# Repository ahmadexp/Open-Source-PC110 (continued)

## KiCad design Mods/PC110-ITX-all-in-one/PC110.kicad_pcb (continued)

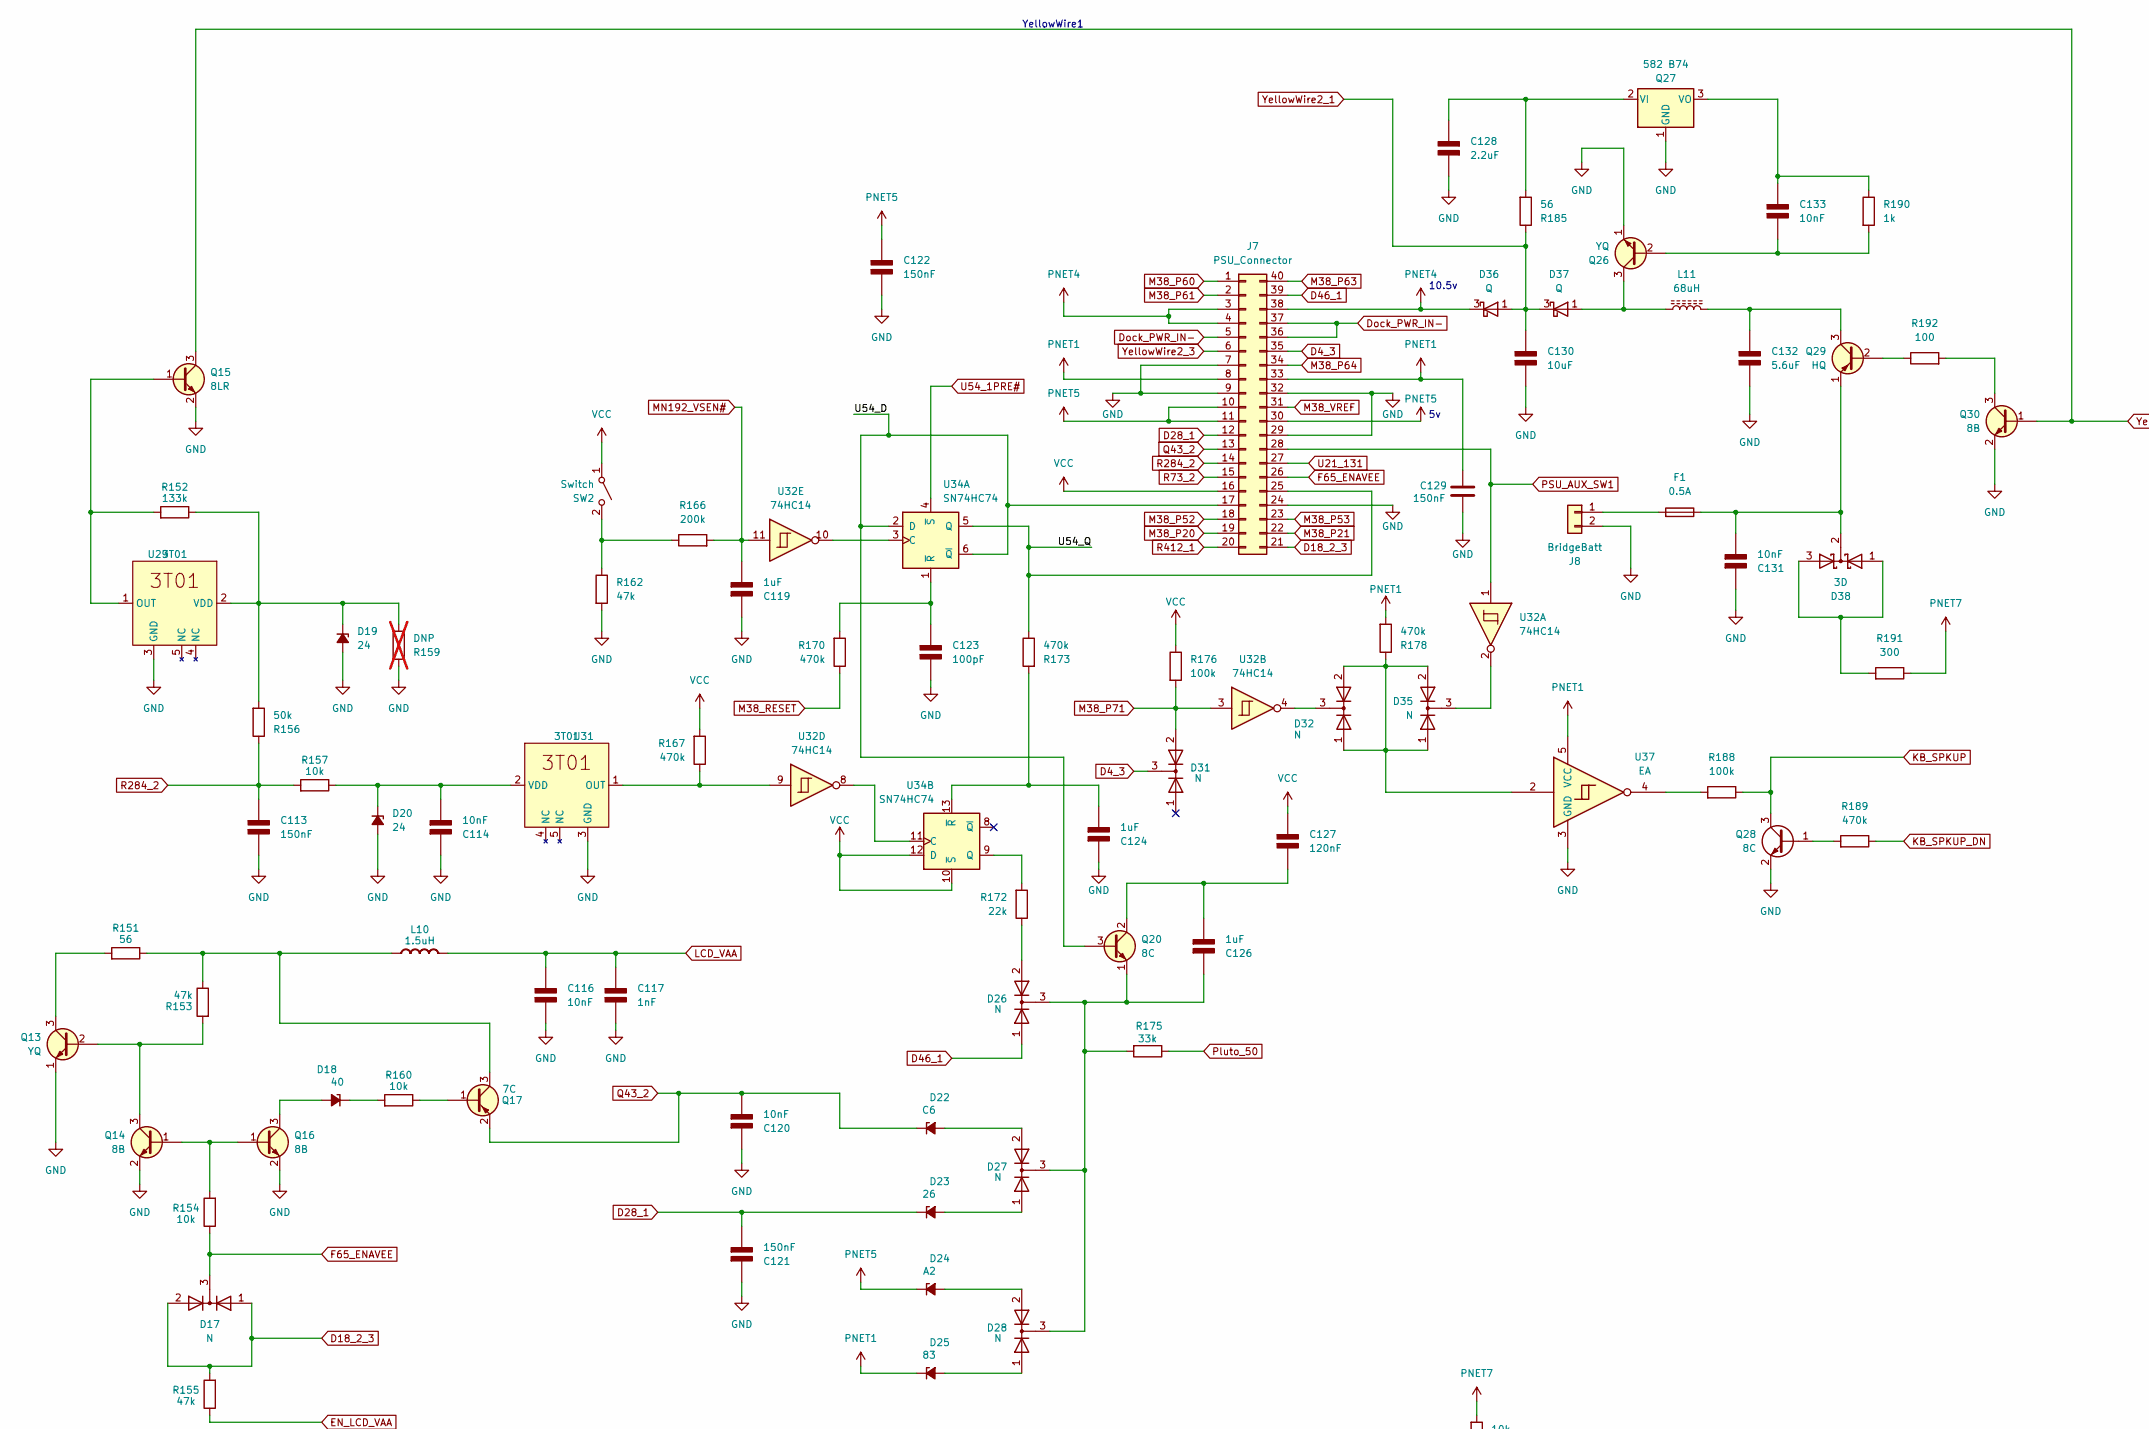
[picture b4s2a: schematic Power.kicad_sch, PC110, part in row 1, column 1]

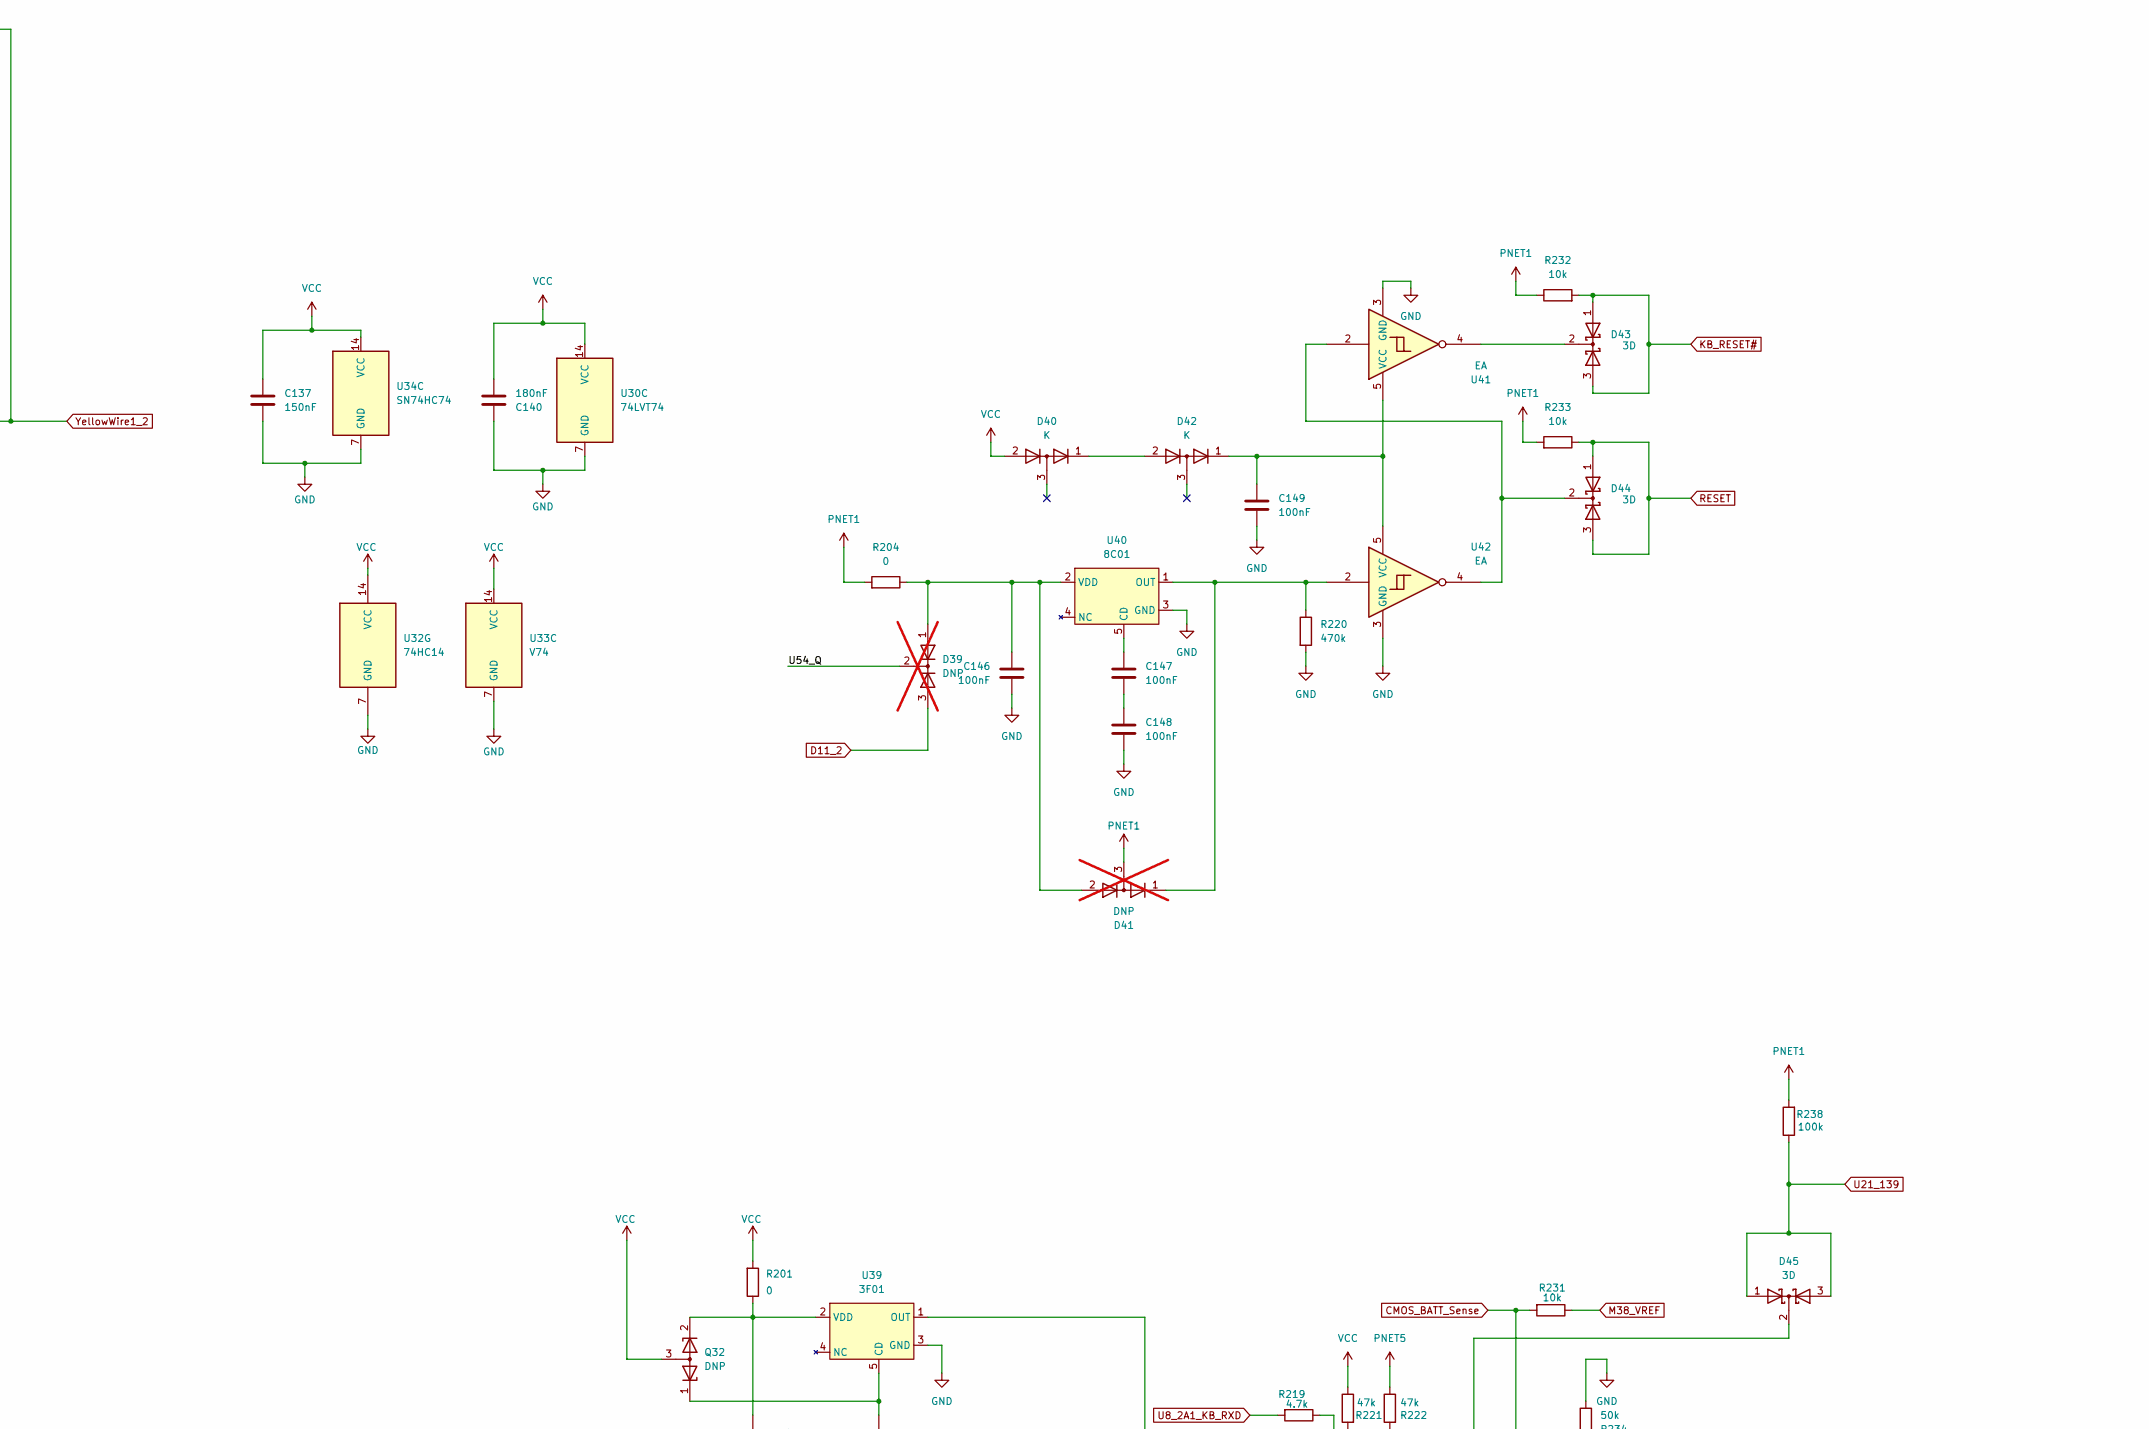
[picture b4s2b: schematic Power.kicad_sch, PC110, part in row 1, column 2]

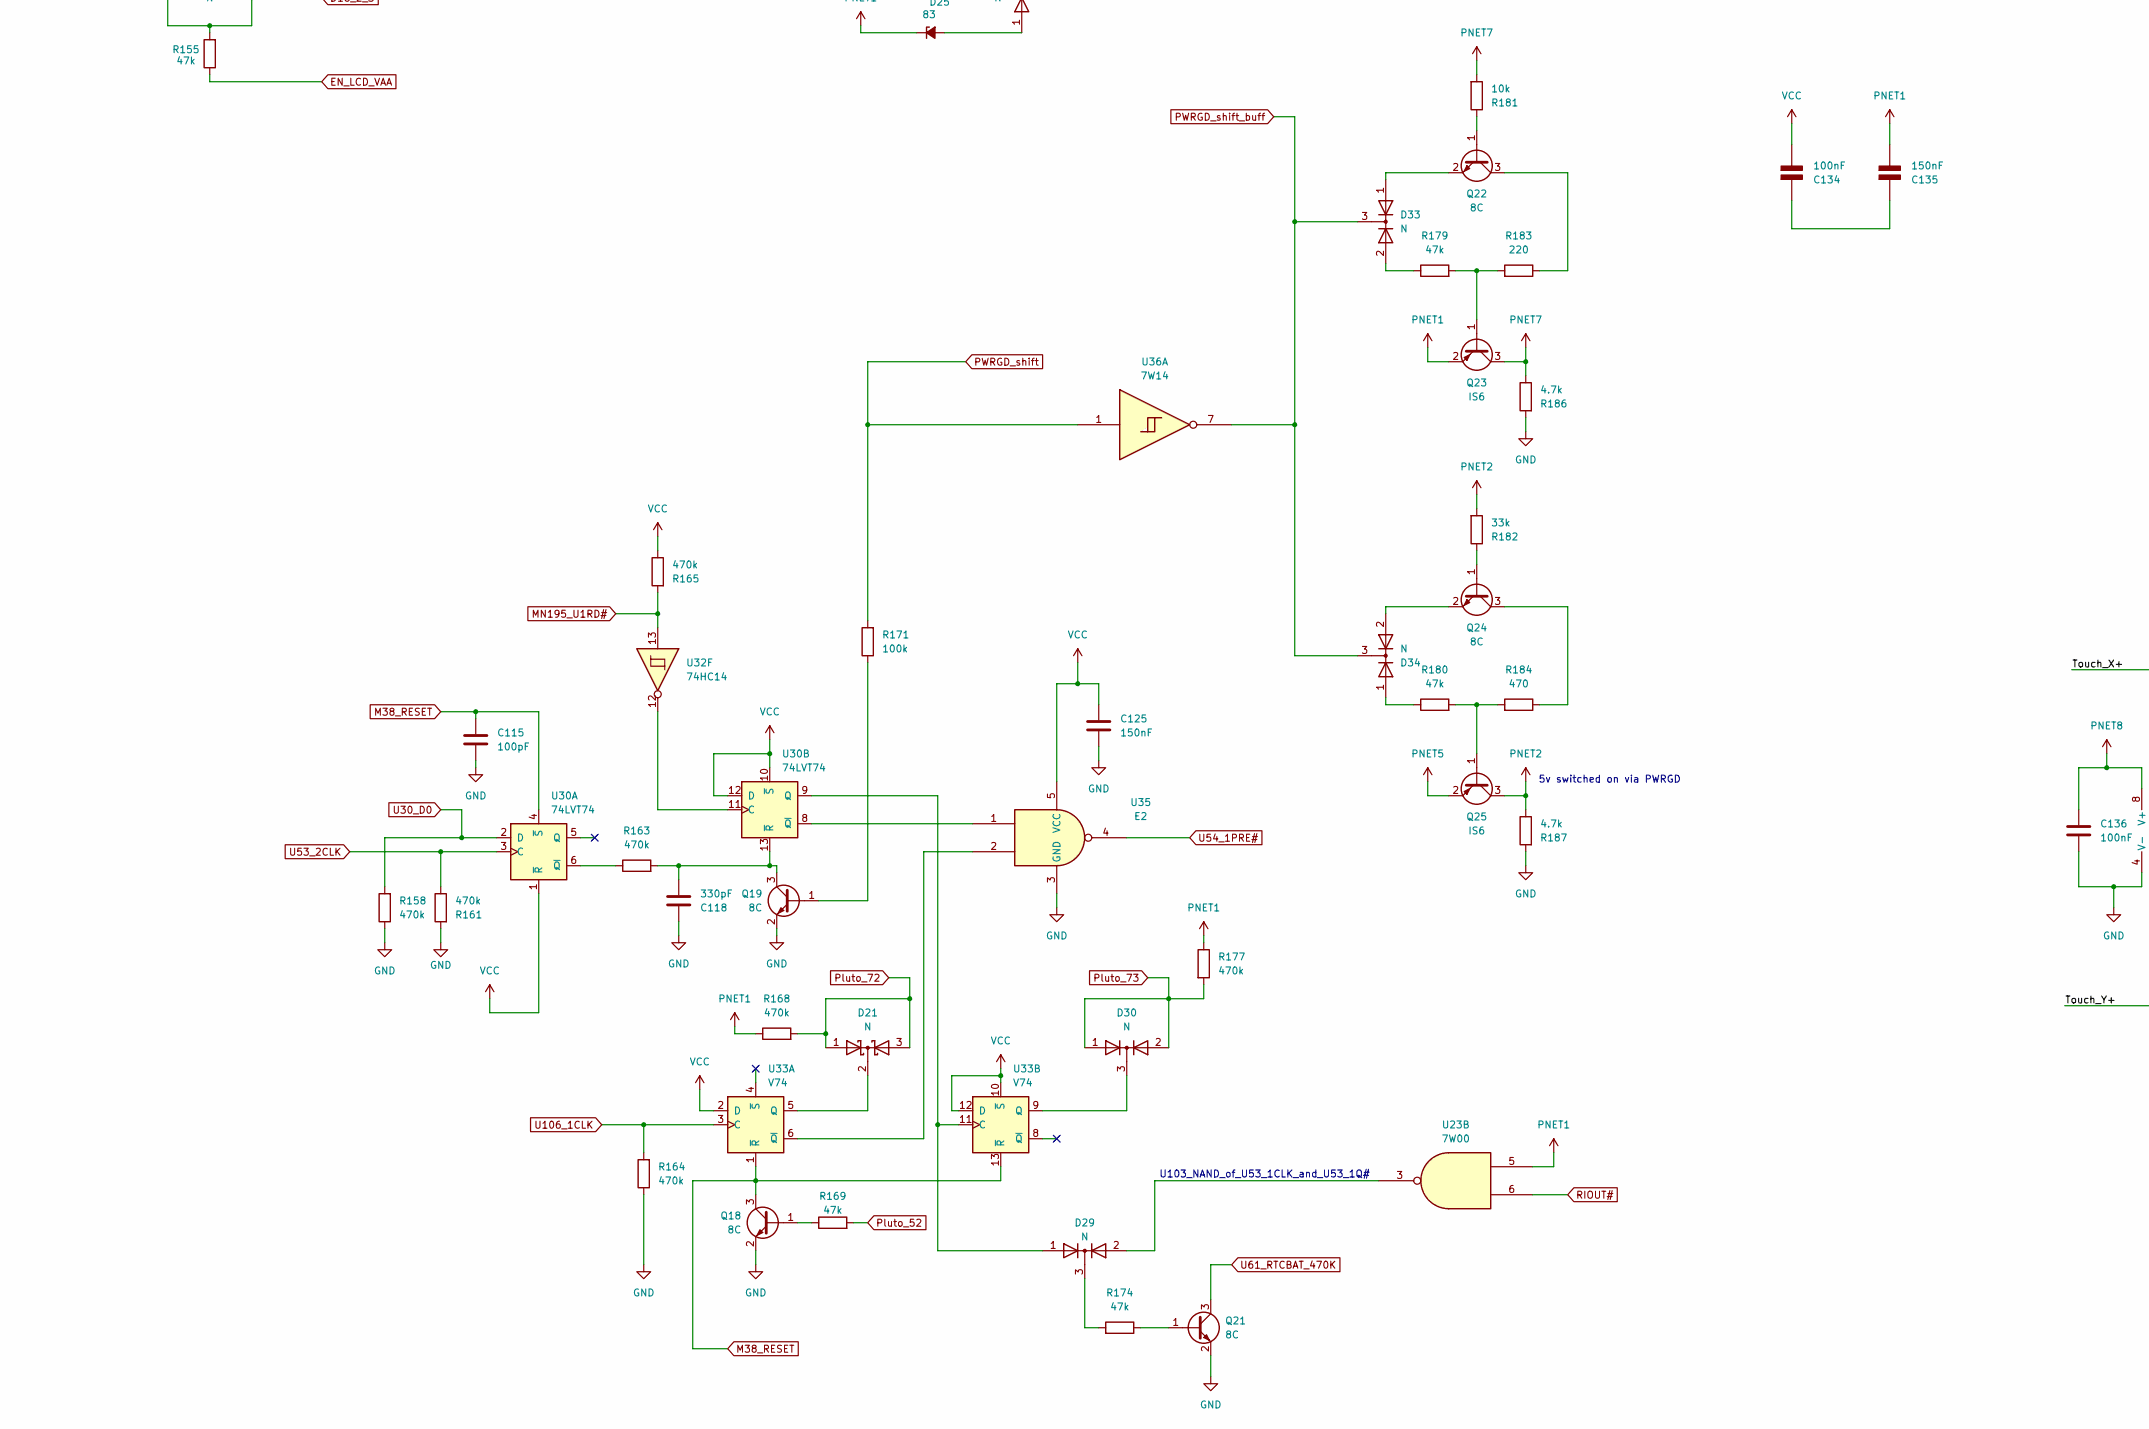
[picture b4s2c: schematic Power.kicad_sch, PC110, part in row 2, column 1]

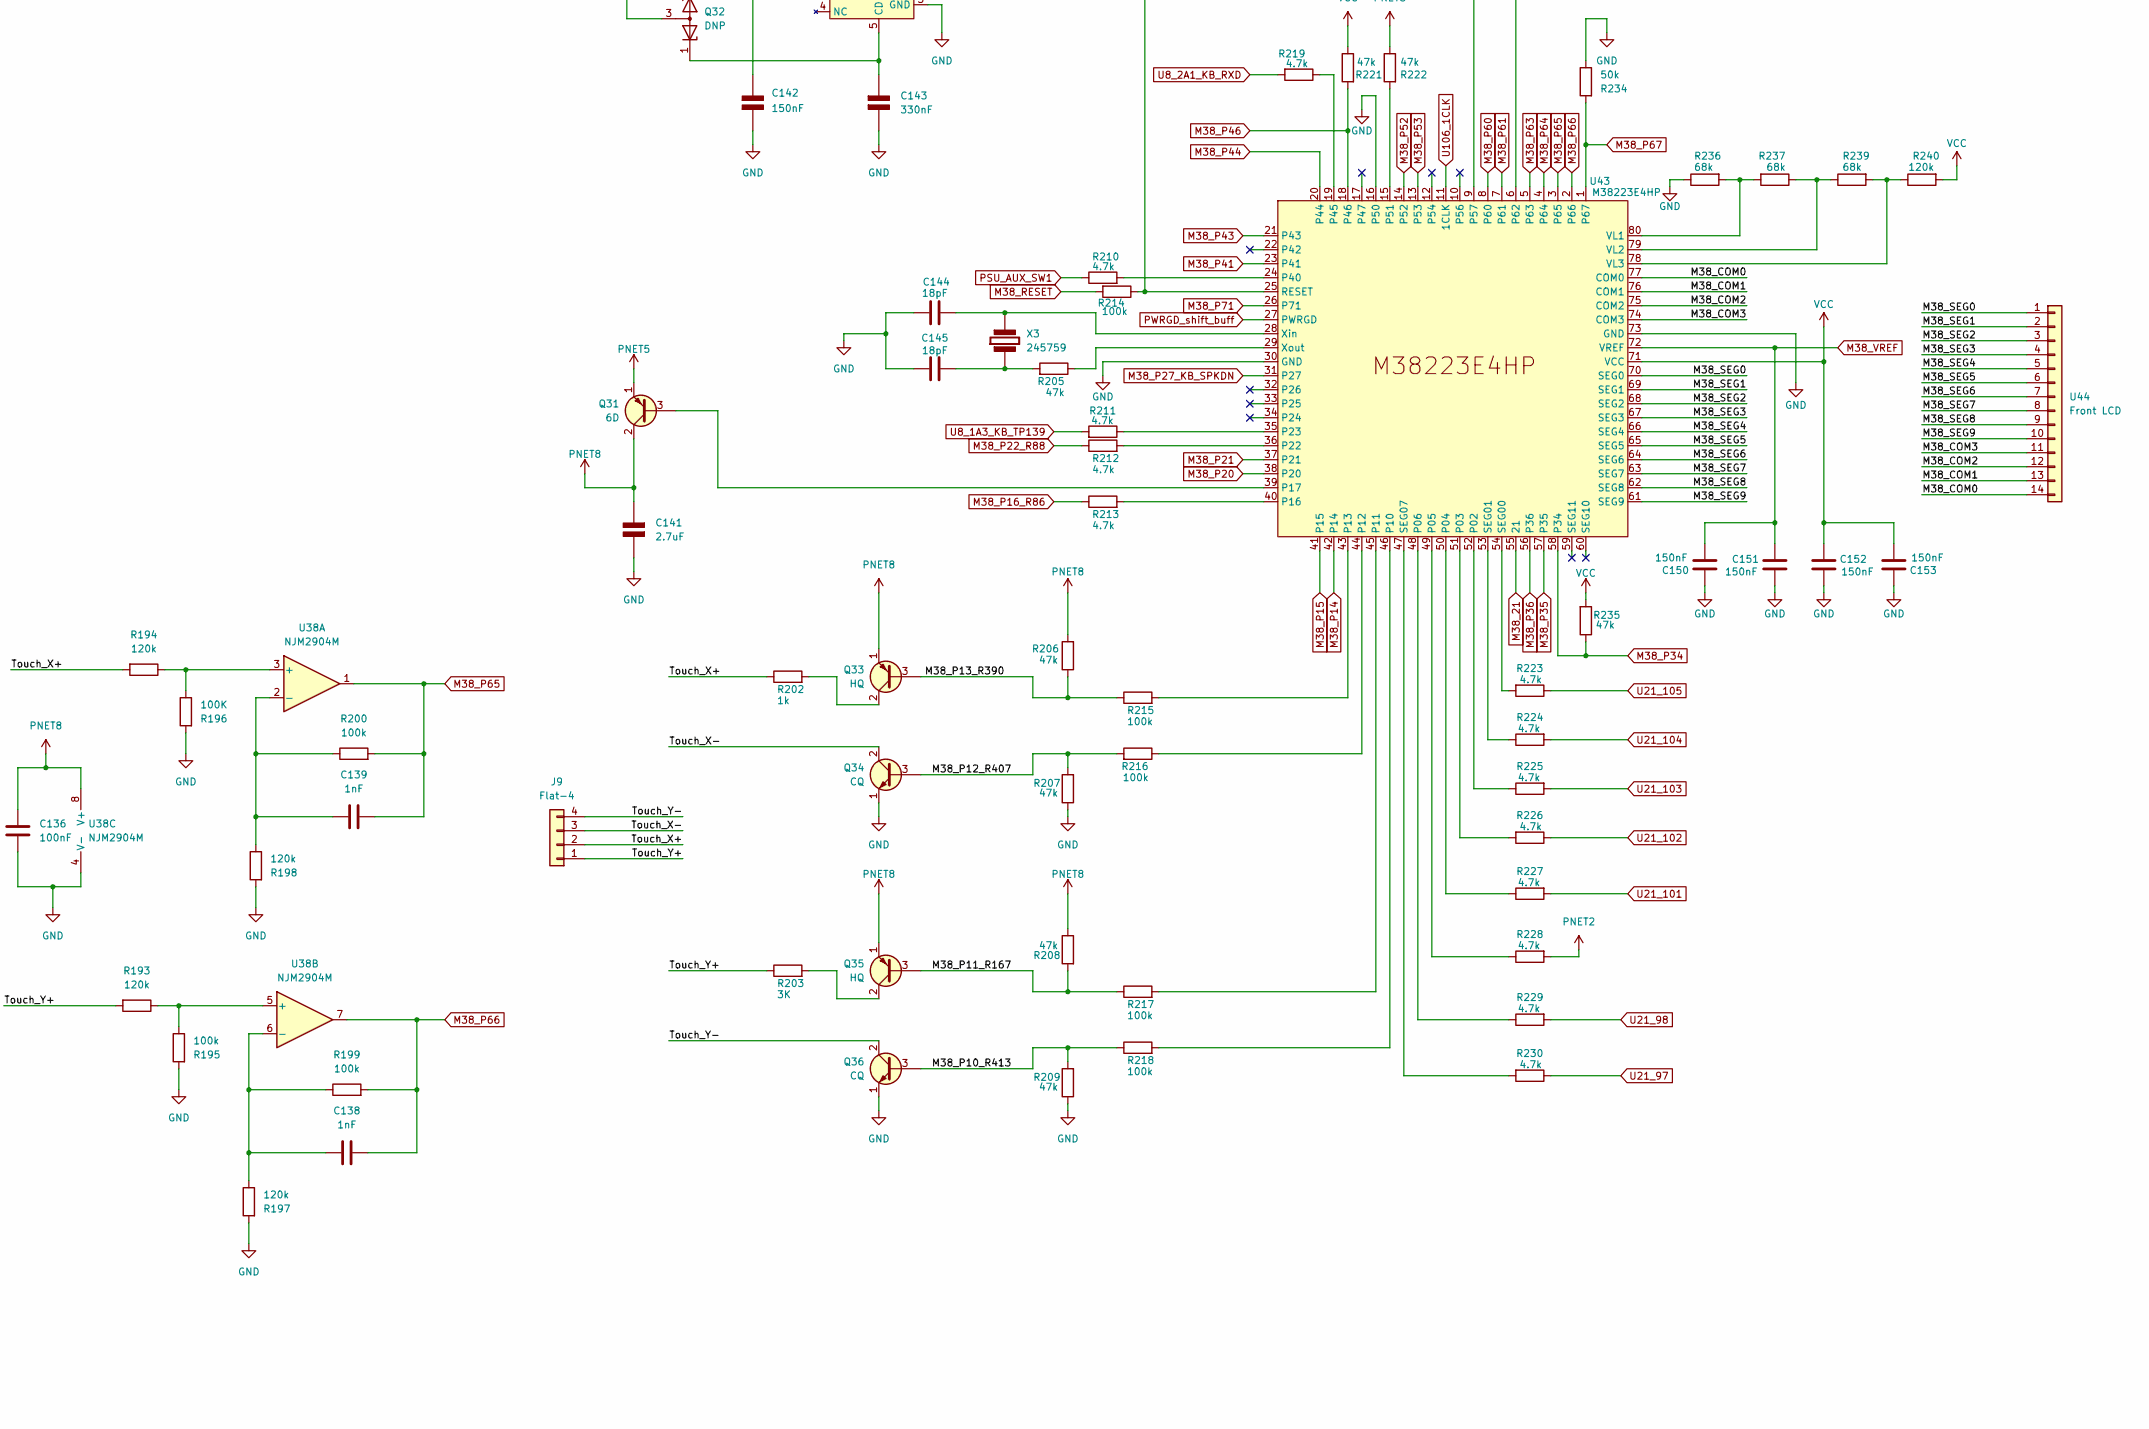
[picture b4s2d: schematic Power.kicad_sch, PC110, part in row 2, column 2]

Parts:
C113, C121: 150nF; C_0603_1608Metric
C114, C116, C120, C131, C133: 10nF; C_0603_1608Metric
C115, C123: 100pF; C_0402_1005Metric
C117, C138, C139: 1nF; C_0402_1005Metric
C118: 330pF; C_0402_1005Metric
C119, C124, C126: 1uF; C_0603_1608Metric
C122, C125, C129, C135, C137, C142, C150, C151, C152, C153: 150nF; C_0402_1005Metric
C127: 120nF; C_0402_1005Metric
C128: 2.2uF; C_0805_2012Metric
C130: 10uF; C_1206_3216Metric
C132: 5.6uF; C_1206_3216Metric
C134, C136, C146, C149: 100nF; C_0402_1005Metric
C140: 180nF; C_0402_1005Metric
C141: 2.7uF; C_0805_2012Metric
C143: 330nF; C_0603_1608Metric
C144, C145: 18pF; C_0402_1005Metric
C147, C148: 100nF; C_0603_1608Metric
D17, D21, D26, D27, D28, D29, D30, D31, D32, D33, D34, D35: N; SOT-416L
D18: 40; D_0603_1608Metric
D19, D20: 24; D_0603_1608Metric
D22: C6; D_0603_1608Metric
D23: 26; D_0603_1608Metric
D24: A2; D_0603_1608Metric
D25: 83; D_0603_1608Metric
D36, D37: Q; 3D
D38, D43, D44: 3D
D39, D41: DNP; 3D; not fitted
D40, D42: K; SOT-416L
D45: 3D; SOT-23
F1: 0.5A; Fuse_1206_3216Metric
J7: PSU_Connector
J8: BridgeBatt
J9: Flat-4
L10: 1.5uH; L_0603_1608Metric
L11: 68uH; L_1210_3225Metric
Q13, Q26: YQ; SOT-416L
Q14, Q16, Q30: 8B; SOT-416
Q15: 8LR; SOT-416
Q17: 7C; TSOT-23
Q18, Q19, Q20, Q21, Q22, Q28: 8C; SOT-416
Q23, Q25: IS6; SOT-23
Q24: 8C; SOT-523
Q27: 582 B74; SOT-89-3
Q29: HQ; SOT-416L
Q31: 6D; 3D
Q32: DNP; SOT-23
Q33, Q35: HQ; TSOT-23
Q34, Q36: CQ; TSOT-23
R151: 56; R_0603_1608Metric
R152: 133k; R_0402_1005Metric
R153, R155, R162, R169, R174, R179, R180, R205, R206, R207, R208, R209, R221, R222, R235: 47k; R_0402_1005Metric
R154, R157, R160, R181, R231, R232, R233: 10k; R_0402_1005Metric
R156, R234: 50k; R_0402_1005Metric
R158, R161, R163, R164, R165, R167, R168, R170, R173, R177, R178, R189, R220: 470k; R_0402_1005Metric
R159: DNP; R_0402_1005Metric; not fitted
R166: 200k; R_0402_1005Metric
R171, R176, R188, R195, R199, R200, R214, R215, R216, R217, R218, R238: 100k; R_0402_1005Metric
R172: 22k; R_0402_1005Metric
R175, R182: 33k; R_0402_1005Metric
R183: 220; R_0402_1005Metric
R184: 470; R_0402_1005Metric
R185: 56; R_0805_2012Metric
R186, R187, R210, R211, R212, R213, R219, R223, R224, R225, R226, R227, R228, R229, R230: 4.7k; R_0402_1005Metric
R190, R202: 1k; R_0402_1005Metric
R191: 300; R_0805_2012Metric
R192: 100; R_0603_1608Metric
R193, R194, R197, R198, R240: 120k; R_0402_1005Metric
R196: 100K; R_0402_1005Metric
R201, R204: 0; R_0402_1005Metric
R203: 3K; R_0402_1005Metric
R236, R237, R239: 68k; R_0402_1005Metric
SW2: Switch
U23: 7W00; sso-8
U29: 3T01; SOT-23-5
U30: 74LVT74; TSSOP-14_4.4x5mm_P0.65mm
U31: 3T01; TSOP-5_1.65x3.05mm_P0.95mm
U32: 74HC14; TSSOP-14_4.4x5mm_P0.65mm
U33: V74; TSSOP-14_4.4x5mm_P0.65mm
U34: SN74HC74; TSSOP-14_4.4x5mm_P0.65mm
U35: E2; SOT-353
U36: 7W14; sso-8
U37, U41, U42: EA; SOT-353
U38: NJM2904M; soic-8-small
U39: 3F01; TSOP-5_1.65x3.05mm_P0.95mm
U40: 8C01; SOT-23-5
U43: M38223E4HP; QFN-80
U44: Front LCD; LCD
X3: 245759; XTAL-2

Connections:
/Power/M38_COM0: U43.77 (COM0), U44.14
/Power/M38_COM1: U43.76 (COM1), U44.13
/Power/M38_COM2: U43.75 (COM2), U44.12
/Power/M38_COM3: U43.74 (COM3), U44.11
/Power/M38_P10_R413: Q36.3 (B), R209.2, R218.1
/Power/M38_P11_R167: Q35.3 (B), R208.2, R217.1
/Power/M38_P12_R407: Q34.3 (B), R207.2, R216.2
/Power/M38_P13_R390: Q33.3 (B), R206.1, R215.1
/Power/M38_SEG0: U43.70 (SEG0), U44.1
/Power/M38_SEG1: U43.69 (SEG1), U44.2
/Power/M38_SEG2: U43.68 (SEG2), U44.3
/Power/M38_SEG3: U43.67 (SEG3), U44.4
/Power/M38_SEG4: U43.66 (SEG4), U44.5
/Power/M38_SEG5: U43.65 (SEG5), U44.6
/Power/M38_SEG6: U43.64 (SEG6), U44.7
/Power/M38_SEG7: U43.63 (SEG7), U44.8
/Power/M38_SEG8: U43.62 (SEG8), U44.9
/Power/M38_SEG9: U43.61 (SEG9), U44.10
/Power/Touch_X+: J9.2, R194.2, R202.1
/Power/Touch_X-: J9.3, Q34.2 (C)
/Power/Touch_Y+: J9.1, R193.2, R203.1
/Power/Touch_Y-: J9.4, Q36.2 (C)
/Power/U54_D: J7.17, Q20.3 (B), U34.2 (D), U34.6 (~Q)
/Power/U54_Q: D39.2 (K), J7.25, R173.1, U34.5 (Q)
CMOS_BATT_Sense: R231.2, U43.6 (P62); also elsewhere on the board
D4_3: D31.3, J7.35; also elsewhere on the board
D11_2: D39.3 (A); also elsewhere on the board
D18_2_3: D17.1, D17.2, J7.21, R155.2; also elsewhere on the board
D28_1: C121.2 (-), D23.1 (K), J7.12; also elsewhere on the board
D46_1: D26.1, J7.39; also elsewhere on the board
Dock_PWR_IN-: J7.5, J7.36, J7.37; also elsewhere on the board
EN_LCD_VAA: R155.1; also elsewhere on the board
F65_ENAVEE: D17.3, J7.26, R154.1; also elsewhere on the board
GND: C113.2 (-), C114.1 (+), C115.1, C116.2 (-), C117.2 (-), C118.2, C119.1 (+), C120.1 (+), C121.1 (+), C122.2 (-), C123.2 (-), C124.1 (+), C125.1, C128.1 (+), C129.2, C130.2 (-), C131.1 (+), C132.2 (-), C136.1, C137.1, C140.2, C141.2 (-), C142.1 (+), C143.2 (-), C144.2, C145.2, C146.1, C148.1, C149.1, C150.1, C151.2, C152.2, C153.1, D19.2 (A), D20.2 (A), J7.7, J7.9, J7.24, J7.29, J7.32, J8.2, Q13.1 (E), Q14.2 (E), Q15.2 (E), Q16.2 (E), Q18.2 (E), Q19.2 (E), Q21.2 (E), Q26.1 (E), Q27.1 (GND), Q28.2 (E), Q30.2 (E), Q34.1 (E), Q36.1 (E), R158.1, R159.1, R161.2, R162.2, R164.1, R186.2, R187.2, R195.2, R196.2, R197.2, R198.2, R207.1, R209.1, R220.2, R234.1, R236.1, U29.3 (GND), U30.7 (GND), U31.3 (GND), U32.7 (GND), U33.7 (GND), U34.7 (GND), U35.3 (GND), U37.3 (GND), U38.4 (V-), U39.3 (GND), U40.3 (GND), U41.3 (GND), U42.3 (GND), U43.16 (P50), U43.30 (GND), U43.73 (GND); also elsewhere on the board
KB_RESET#: D43.1 (A), D43.3 (A), R232.2; also elsewhere on the board
KB_SPKUP: Q28.3 (C), R188.1; also elsewhere on the board
KB_SPKUP_DN: R189.1; also elsewhere on the board
LCD_VAA: C116.1 (+), C117.1 (+), L10.1 (+); also elsewhere on the board
M38_21: U43.55 (21); also elsewhere on the board
M38_P14: U43.42 (P14); also elsewhere on the board
M38_P15: U43.41 (P15); also elsewhere on the board
M38_P16_R86: R213.1
M38_P20: J7.19, U43.38 (P20); also elsewhere on the board
M38_P21: J7.22, U43.37 (P21); also elsewhere on the board
M38_P22_R88: R212.1; also elsewhere on the board
M38_P27_KB_SPKDN: U43.31 (P27); also elsewhere on the board
M38_P35: U43.57 (P35); also elsewhere on the board
M38_P36: U43.56 (P36); also elsewhere on the board
M38_P41: U43.23 (P41); also elsewhere on the board
M38_P43: U43.21 (P43); also elsewhere on the board
M38_P44: U43.20 (P44); also elsewhere on the board
M38_P52: J7.18, U43.14 (P52); also elsewhere on the board
M38_P53: J7.23, U43.13 (P53); also elsewhere on the board
M38_P60: J7.1, U43.8 (P60); also elsewhere on the board
M38_P61: J7.2, U43.7 (P61); also elsewhere on the board
M38_P63: J7.40, U43.5 (P63); also elsewhere on the board
M38_P64: J7.34, U43.4 (P64); also elsewhere on the board
M38_P65: C139.2, R200.2, U38.1, U43.3 (P65)
M38_P66: C138.2, R199.2, U38.7, U43.2 (P66)
M38_P67: R234.2, U43.1 (P67)
M38_P71: D31.2, R176.2, U32.3, U43.26 (P71)
M38_RESET: C115.2, Q18.3 (C), R170.1, R214.2, U30.4 (~S), U33.1 (~R), U33.13 (~R)
M38_VREF: C150.2, C151.1, J7.31, R231.1, U43.72 (VREF); also elsewhere on the board
MN192_VSEN#: C119.2 (-), R166.2, U32.11; also elsewhere on the board
MN195_U1RD#: R165.2, U32.13; also elsewhere on the board
unnamed: C114.2 (-), D20.1 (K), R157.1, U31.2 (VDD)
unnamed: C123.1 (+), R170.2, U34.1 (~R)
unnamed: C124.2 (-), R173.2, U34.13 (~R)
unnamed: C126.1 (+), D26.3, D27.3, D28.3, Q20.1 (E), R175.2
unnamed: C126.2 (-), C127.2 (-), Q20.2 (C)
unnamed: C128.2 (-), Q27.2 (VI), R185.2
unnamed: C131.2 (-), D38.2 (K), F1.1, Q29.1 (E)
unnamed: C132.1 (+), L11.1, Q29.3 (C)
unnamed: C133.1 (+), Q27.3 (VO), R190.1
unnamed: C133.2 (-), Q26.2 (B), R190.2
unnamed: C134.1 (+), C135.1 (+)
unnamed: C142.2 (-), Q32.2 (K), R201.1, U39.2 (VDD)
unnamed: C143.1 (+), Q32.1 (K), U39.5 (CD)
unnamed: C147.1, C148.2
unnamed: D18.2 (A), Q16.3 (C)
unnamed: D18.1 (K), R160.2
unnamed: D19.1 (K), R152.1, R156.2, R159.2, U29.2 (VDD)
unnamed: D21.2 (K), U33.5 (Q)
unnamed: D22.2 (A), D27.2
unnamed: D23.2 (A), D27.1
unnamed: D24.2 (A), D28.2
unnamed: D25.2 (A), D28.1
unnamed: D26.2, R172.1
unnamed: D29.2, U23.3
unnamed: D29.3, R174.2
unnamed: D32.1, D32.2, D35.1, D35.2, R178.1, U37.2
unnamed: D32.3, U32.4
unnamed: D33.2, R179.1
unnamed: D34.1, R180.1
unnamed: D35.3, U32.2
unnamed: D37.1 (A), L11.2, Q26.3 (C)
unnamed: D38.1 (A), D38.3 (A), R191.2
unnamed: D40.1 (K), D42.2 (A)
unnamed: C146.2, D39.1 (A), D41.2 (A), R204.1, U40.2 (VDD)
unnamed: D41.1 (K), R220.1, U40.1 (OUT), U42.2
unnamed: C149.2, D42.1 (K), U41.5 (VCC), U42.5 (VCC)
unnamed: D43.2 (K), U41.4
unnamed: D44.2 (K), U41.2, U42.4
unnamed: D45.2 (K), U43.9 (P57)
unnamed: F1.2, J8.1
unnamed: L10.2 (-), Q17.3 (C), R151.1, R153.1
unnamed: Q13.2 (B), Q14.3 (C), R153.2
unnamed: Q13.3 (C), R151.2
unnamed: Q14.1 (B), Q16.1 (B), R154.2
unnamed: Q15.1 (B), R152.2, U29.1 (OUT)
unnamed: Q17.1 (B), R160.1
unnamed: Q18.1 (B), R169.1
unnamed: Q19.1 (B), R171.1
unnamed: C118.1, Q19.3 (C), R163.2, U30.13 (~R)
unnamed: Q21.1 (B), R174.1
unnamed: Q22.1 (B), R181.1
unnamed: Q22.3 (C), R183.1
unnamed: D33.1, Q22.2 (E)
unnamed: Q23.1 (B), R179.2, R183.2
unnamed: Q24.1 (B), R182.1
unnamed: Q24.3 (C), R184.1
unnamed: D34.2, Q24.2 (E)
unnamed: Q25.1 (B), R180.2, R184.2
unnamed: Q28.1 (B), R189.2
unnamed: Q29.2 (B), R192.1
unnamed: Q30.3 (C), R192.2
unnamed: Q31.3 (B), U43.39 (P17)
unnamed: Q33.2 (C), R202.2
unnamed: Q35.2 (C), R203.2
unnamed: R188.2, U37.4
unnamed: R162.1, R166.1, SW2.2 (B)
unnamed: R163.1, U30.6 (~Q)
unnamed: U30.11 (C), U32.12
unnamed: D29.1, U30.9 (Q), U33.11 (C)
unnamed: U30.8 (~Q), U35.1
unnamed: R167.1, U31.1 (OUT), U32.9
unnamed: U33.6 (~Q), U35.2
unnamed: D30.3, U33.9 (Q)
unnamed: U32.10, U34.3 (C)
unnamed: U32.8, U34.11 (C)
unnamed: R172.2, U34.9 (Q)
unnamed: R194.1, R196.1, U38.3 (+)
unnamed: C139.1, R198.1, R200.1, U38.2 (-)
unnamed: R193.1, R195.1, U38.5 (+)
unnamed: C138.1, R197.1, R199.1, U38.6 (-)
unnamed: R214.1, U39.1 (OUT), U43.25 (RESET)
unnamed: C147.2, U40.5 (CD)
unnamed: R225.1, U43.52 (P02)
unnamed: R226.2, U43.51 (P03)
unnamed: R227.1, U43.50 (P04)
unnamed: R228.1, U43.49 (P05)
unnamed: R229.1, U43.48 (P06)
unnamed: R218.2, U43.46 (P10)
unnamed: R217.2, U43.45 (P11)
unnamed: R216.1, U43.44 (P12)
unnamed: R215.2, U43.43 (P13)
unnamed: R213.2, U43.40 (P16)
unnamed: R212.2, U43.36 (P22)
unnamed: R211.1, U43.35 (P23)
unnamed: R210.2, U43.24 (P40)
unnamed: R219.1, U43.19 (P45)
unnamed: R222.2, U43.15 (P51)
unnamed: R223.2, U43.54 (SEG00)
unnamed: R224.1, U43.53 (SEG01)
unnamed: R230.2, U43.47 (SEG07)
unnamed: R236.2, R237.2, U43.80 (VL1)
unnamed: R237.1, R239.1, U43.79 (VL2)
unnamed: R239.2, R240.1, U43.78 (VL3)
unnamed: C144.1, U43.28 (Xin), X3.1 (+)
unnamed: R205.1, U43.29 (Xout)
unnamed: C145.1, R205.2, X3.2 (-)
PNET1: C129.1, C135.2 (-), D25.1 (K), D41.3 (common), J7.8, J7.33, Q23.2 (E), R168.1, R177.1, R178.2, R204.2, R232.1, R233.2, R238.2, U23.5, U37.5 (VCC); also elsewhere on the board
PNET2: Q25.3 (C), R182.2, R187.1, R228.2; also elsewhere on the board
PNET4: D36.3 (K), J7.3, J7.4, J7.38; also elsewhere on the board
PNET5: C122.1 (+), D24.1 (K), J7.10, J7.11, J7.30, Q25.2 (E), Q31.1 (E), R222.1; also elsewhere on the board
PNET7: Q23.3 (C), R181.2, R186.1, R191.1; also elsewhere on the board
PNET8: C136.2, C141.1 (+), Q31.2 (C), Q33.1 (E), Q35.1 (E), R206.2, R208.1, U38.8 (V+)
PSU_AUX_SW1: J7.28, R210.1, U32.1; also elsewhere on the board
PWRGD_shift: R171.2, U36.1; also elsewhere on the board
PWRGD_shift_buff: D33.3, D34.3, U36.7, U43.27 (PWRGD); also elsewhere on the board
Pluto_50: R175.1; also elsewhere on the board
Pluto_52: R169.2; also elsewhere on the board
Pluto_72: D21.1 (A), D21.3 (A), R168.2; also elsewhere on the board
Pluto_73: D30.1, D30.2, R177.2; also elsewhere on the board
Q43_2: C120.2 (-), D22.1 (K), J7.13, Q17.2 (E); also elsewhere on the board
R73_2: J7.15; also elsewhere on the board
R284_2: C113.1 (+), J7.14, R156.1, R157.2; also elsewhere on the board
R412_1: J7.20; also elsewhere on the board
RESET: D44.1 (A), D44.3 (A), R233.1; also elsewhere on the board
RIOUT#: U23.6; also elsewhere on the board
U8_1A3_KB_TP139: R211.2; also elsewhere on the board
U8_2A1_KB_RXD: R219.2; also elsewhere on the board
U21_97: R230.1; also elsewhere on the board
U21_98: R229.2; also elsewhere on the board
U21_101: R227.2; also elsewhere on the board
U21_102: R226.1; also elsewhere on the board
U21_103: R225.2; also elsewhere on the board
U21_104: R224.2; also elsewhere on the board
U21_105: R223.1; also elsewhere on the board
U21_131: J7.27; also elsewhere on the board
U21_139: D45.1 (A), D45.3 (A), R238.1; also elsewhere on the board
U30_D0: R158.2, U30.2 (D); also elsewhere on the board
U53_2CLK: R161.1, U30.3 (C); also elsewhere on the board
U54_1PRE#: U34.4 (~S), U35.4
U61_RTCBAT_470K: Q21.3 (C); also elsewhere on the board
U106_1CLK: R164.2, U33.3 (C), U43.11 (1CLK)
VCC: C125.2, C127.1 (+), C134.2 (-), C137.2, C140.1, C152.1, C153.2, D40.2 (A), J7.16, Q32.3 (A), R165.1, R167.2, R176.1, R201.2, R221.1, R235.2, R240.2, SW2.1 (A), U30.1 (~R), U30.10 (~S), U30.12 (D), U30.14 (VCC), U32.14 (VCC), U33.2 (D), U33.10 (~S), U33.12 (D), U33.14 (VCC), U34.10 (~S), U34.12 (D), U34.14 (VCC), U35.5 (VCC), U43.71 (VCC); also elsewhere on the board
YellowWire1_2: Q15.3 (C), Q30.1 (B); also elsewhere on the board
YellowWire2_1: C130.1 (+), D36.1 (A), D37.3 (K), R185.1; also elsewhere on the board
YellowWire2_3: J7.6; also elsewhere on the board

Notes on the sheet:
5v switched on via PWRGD
10.5v
YellowWire1
U103_NAND_of_U53_1CLK_and_U53_1Q#
